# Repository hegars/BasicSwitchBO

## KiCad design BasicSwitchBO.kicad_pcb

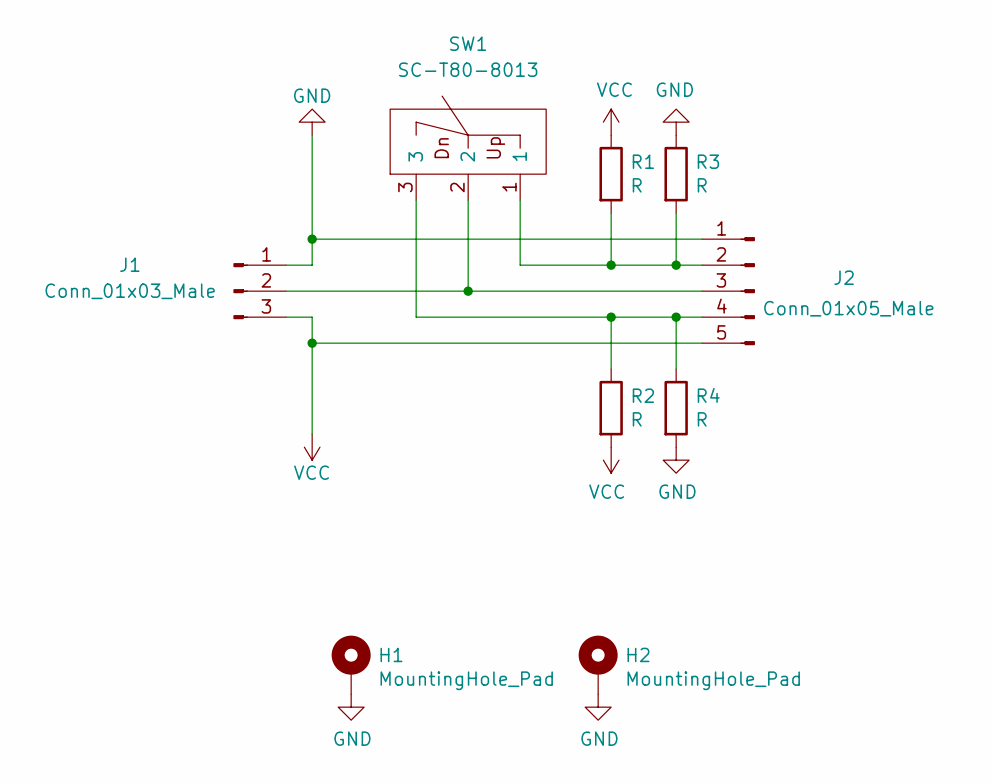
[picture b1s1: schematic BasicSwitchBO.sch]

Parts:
H1, H2: MountingHole_Pad; MountingHole_3.2mm_M3_Pad_Via
J1: Conn_01x03_Male; Pin_Header_Straight_1x03_Pitch2.54mm
J2: Conn_01x05_Male; Pin_Header_Straight_1x05_Pitch2.54mm
R1, R2, R3, R4: R; R_Axial_DIN0204_L3.6mm_D1.6mm_P1.90mm_Vertical
SW1: SC-T80-8013; Salecom T80-T T8013

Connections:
GND: H1.1, H2.1, J1.1, J2.1, R3.1, R4.2
unnamed: J1.2, J2.3, SW1.2
unnamed: J2.2, R1.2, R3.2, SW1.1
unnamed: J2.4, R2.1, R4.1, SW1.3
VCC: J1.3, J2.5, R1.1, R2.2

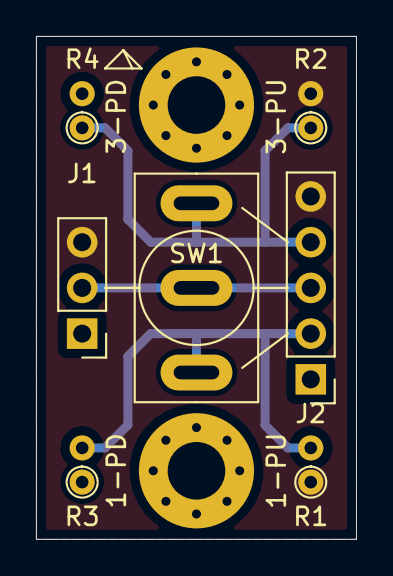
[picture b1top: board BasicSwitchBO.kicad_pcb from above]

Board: 2 copper layers, 17.8 x 27.9 mm, 9 parts (0 on the bottom side), 5 nets.

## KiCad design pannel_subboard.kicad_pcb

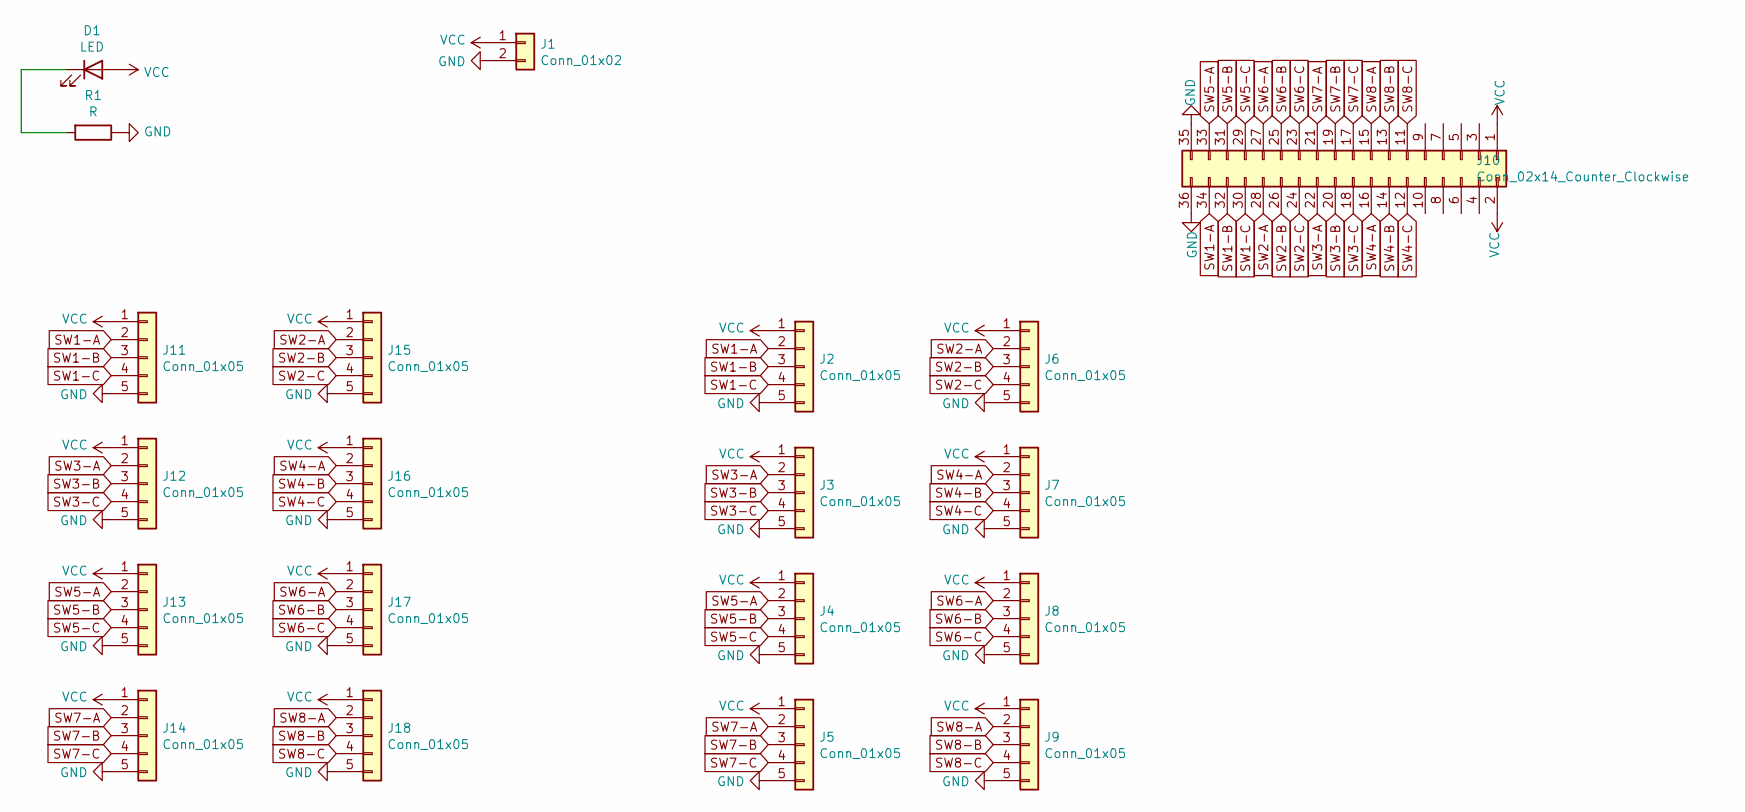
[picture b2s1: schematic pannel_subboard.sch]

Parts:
D1: LED; LED_D3.0mm
J1: Conn_01x02; Pin_Header_Straight_1x02_Pitch2.54mm
J2, J3, J4, J5, J6, J7, J8, J9, J11, J12, J13, J14, J15, J16, J17, J18: Conn_01x05; Pin_Header_Straight_1x05_Pitch2.54mm
J10: Conn_02x14_Counter_Clockwise; Pin_Header_Straight_2x18_Pitch2.54mm
R1: R; R_Axial_DIN0204_L3.6mm_D1.6mm_P1.90mm_Vertical

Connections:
GND: J1.2, J2.5, J3.5, J4.5, J5.5, J6.5, J7.5, J8.5, J9.5, J10.35, J10.36, J11.5, J12.5, J13.5, J14.5, J15.5, J16.5, J17.5, J18.5, R1.1
unnamed: D1.1 (K), R1.2
SW1-A: J2.2, J10.34, J11.2
SW1-B: J2.3, J10.32, J11.3
SW1-C: J2.4, J10.30, J11.4
SW2-A: J6.2, J10.28, J15.2
SW2-B: J6.3, J10.26, J15.3
SW2-C: J6.4, J10.24, J15.4
SW3-A: J3.2, J10.22, J12.2
SW3-B: J3.3, J10.20, J12.3
SW3-C: J3.4, J10.18, J12.4
SW4-A: J7.2, J10.16, J16.2
SW4-B: J7.3, J10.14, J16.3
SW4-C: J7.4, J10.12, J16.4
SW5-A: J4.2, J10.33, J13.2
SW5-B: J4.3, J10.31, J13.3
SW5-C: J4.4, J10.29, J13.4
SW6-A: J8.2, J10.27, J17.2
SW6-B: J8.3, J10.25, J17.3
SW6-C: J8.4, J10.23, J17.4
SW7-A: J5.2, J10.21, J14.2
SW7-B: J5.3, J10.19, J14.3
SW7-C: J5.4, J10.17, J14.4
SW8-A: J9.2, J10.15, J18.2
SW8-B: J9.3, J10.13, J18.3
SW8-C: J9.4, J10.11, J18.4
VCC: D1.2 (A), J1.1, J2.1, J3.1, J4.1, J5.1, J6.1, J7.1, J8.1, J9.1, J10.1, J10.2, J11.1, J12.1, J13.1, J14.1, J15.1, J16.1, J17.1, J18.1

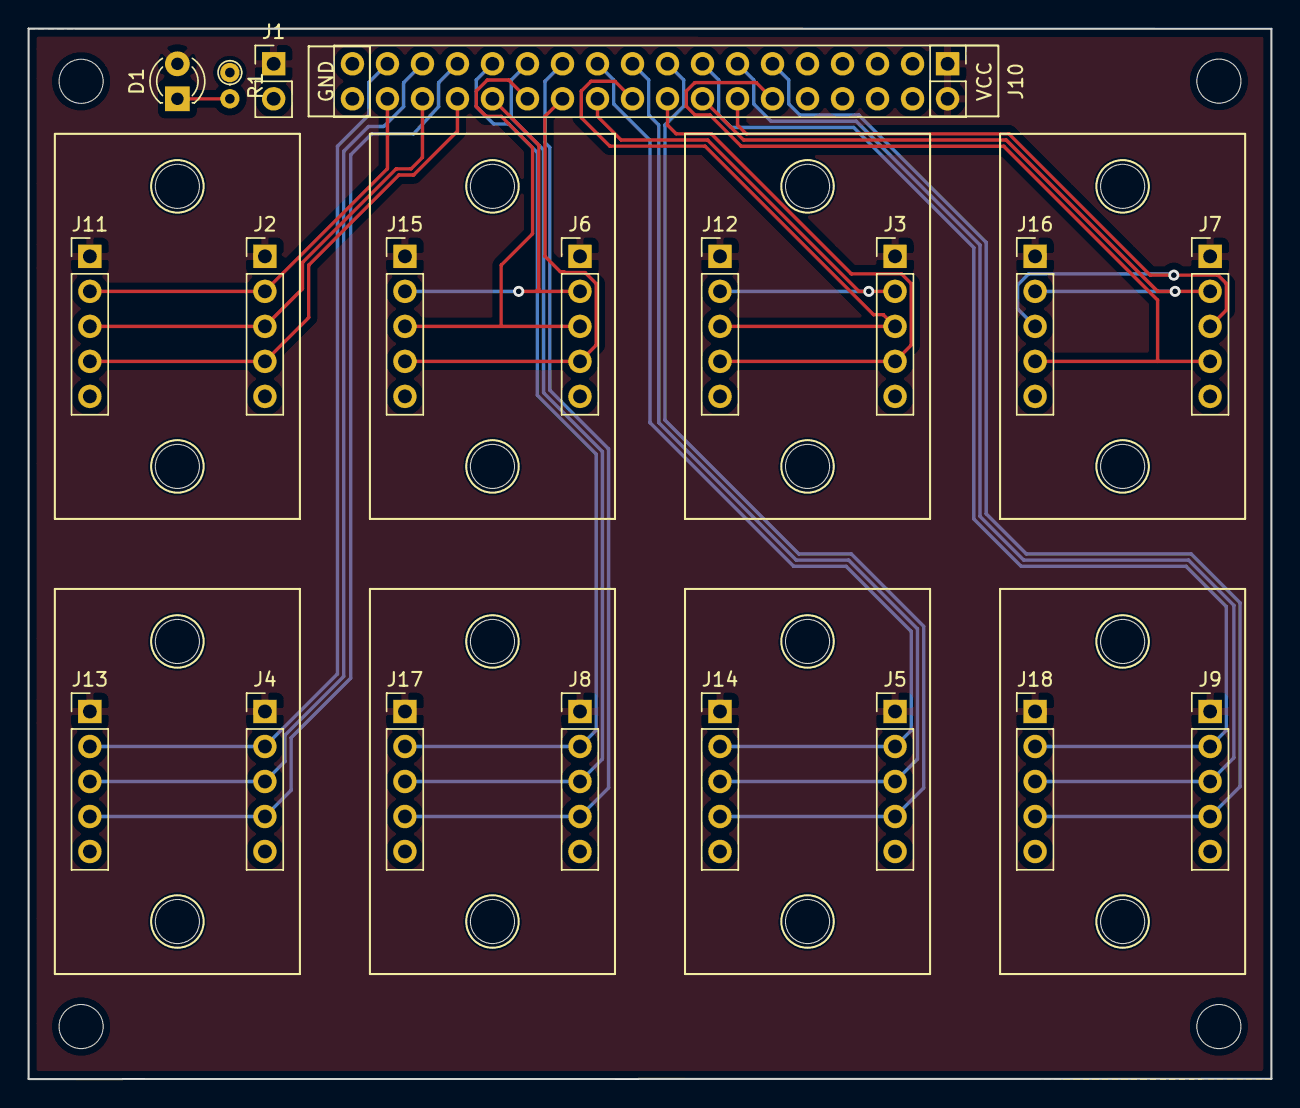
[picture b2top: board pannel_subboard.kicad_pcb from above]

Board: 2 copper layers, 90.2 x 76.2 mm, 20 parts (0 on the bottom side), 27 nets.

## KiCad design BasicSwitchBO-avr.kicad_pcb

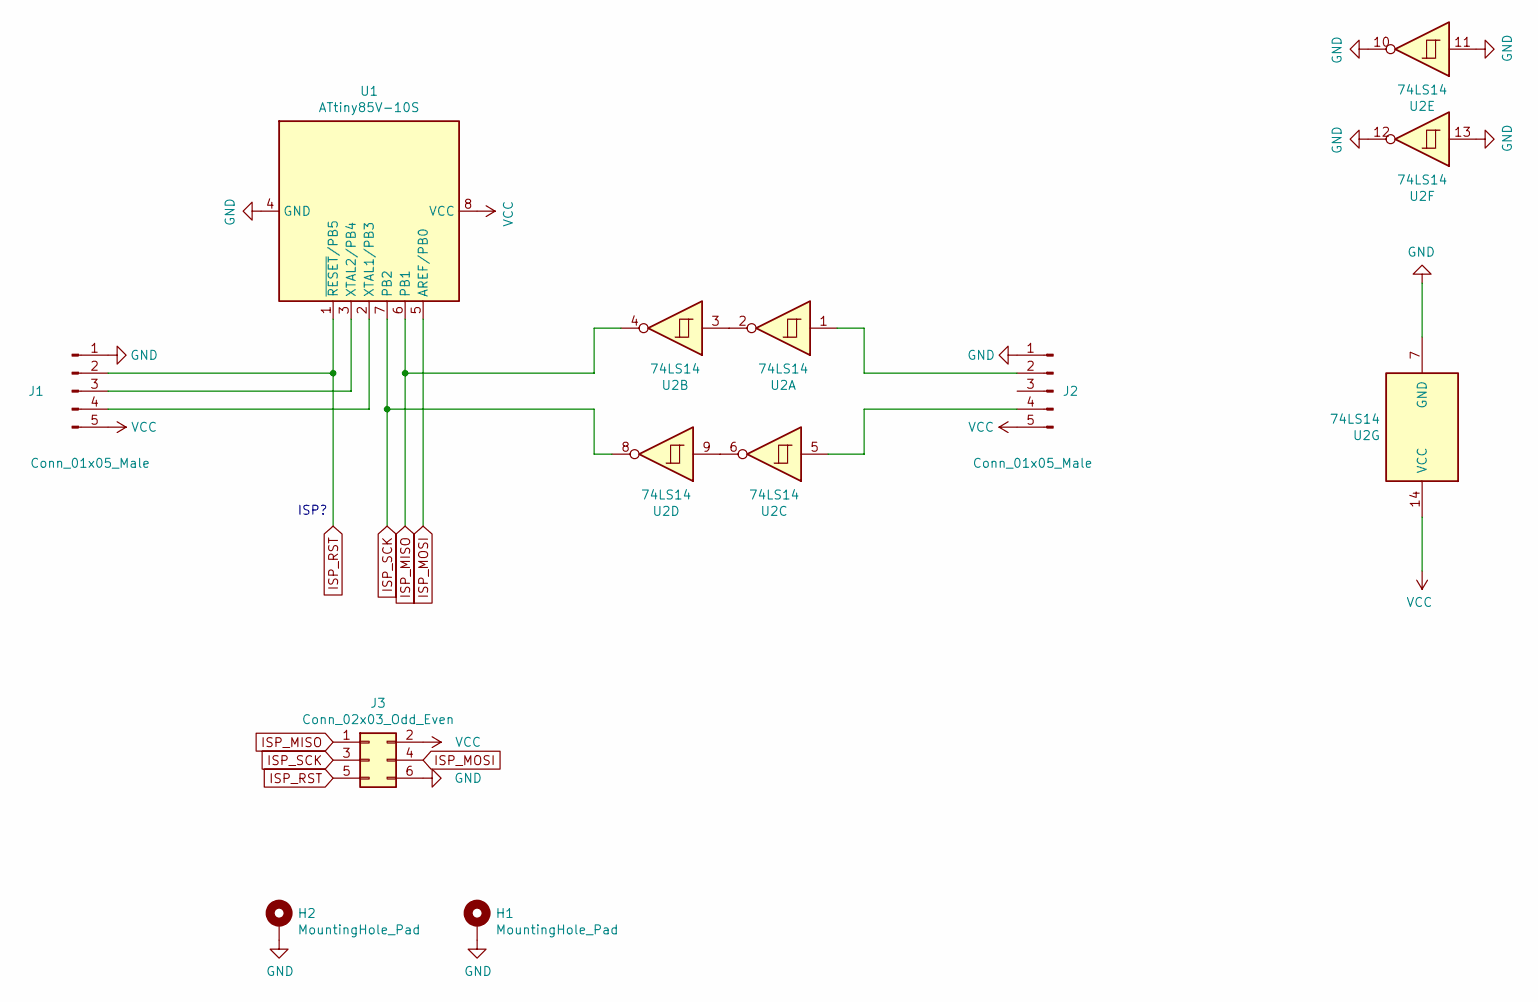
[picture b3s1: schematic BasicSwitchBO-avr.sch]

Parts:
H1, H2: MountingHole_Pad; MountingHole_3.2mm_M3_Pad_Via
J1, J2: Conn_01x05_Male; Pin_Header_Straight_1x05_Pitch2.54mm
J3: Conn_02x03_Odd_Even; Pin_Header_Straight_2x03_Pitch1.27mm
U1: ATtiny85V-10S; SOIC-8_3.9x4.9mm_Pitch1.27mm
U2: 74LS14; SOIC-14_3.9x8.7mm_Pitch1.27mm

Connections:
GND: H1.1, H2.1, J1.1, J2.1, J3.6, U1.4 (GND), U2.7 (GND), U2.10, U2.11, U2.12, U2.13
ISP_MISO: J3.1, U1.6 (PB1), U2.4
ISP_MOSI: J3.4, U1.5 (AREF/PB0)
ISP_RST: J1.2, J3.5, U1.1 (~RESET~/PB5)
ISP_SCK: J3.3, U1.7 (PB2), U2.8
unnamed: J1.3, U1.3 (XTAL2/PB4)
unnamed: J1.4, U1.2 (XTAL1/PB3)
unnamed: J2.2, U2.1
unnamed: J2.4, U2.5
unnamed: U2.2, U2.3
unnamed: U2.6, U2.9
VCC: J1.5, J2.5, J3.2, U1.8 (VCC), U2.14 (VCC)

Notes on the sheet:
ISP?

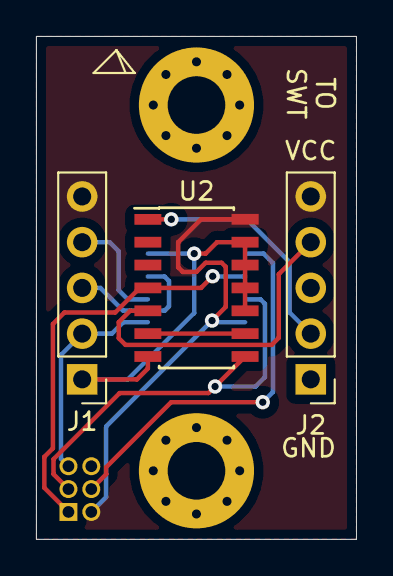
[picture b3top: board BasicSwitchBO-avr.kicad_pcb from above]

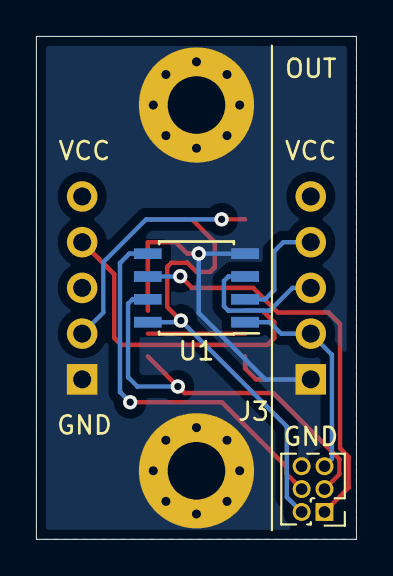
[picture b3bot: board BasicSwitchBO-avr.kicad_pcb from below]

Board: 2 copper layers, 17.8 x 27.9 mm, 7 parts (2 on the bottom side), 12 nets.

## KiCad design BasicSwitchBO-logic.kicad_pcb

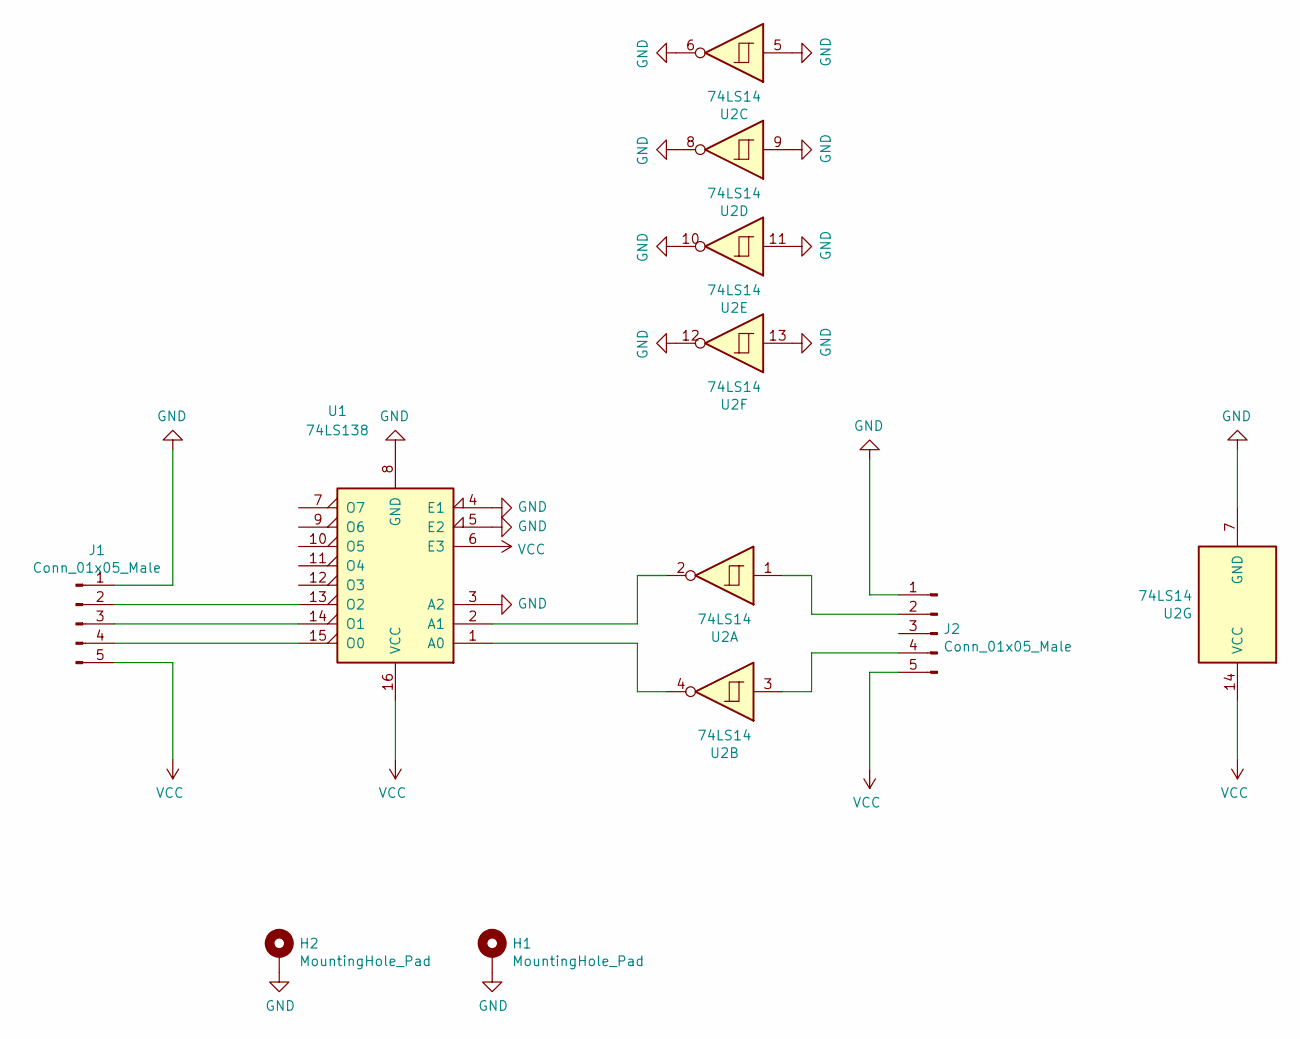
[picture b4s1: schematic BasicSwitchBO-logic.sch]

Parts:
H1, H2: MountingHole_Pad; MountingHole_3.2mm_M3_Pad_Via
J1, J2: Conn_01x05_Male; Pin_Header_Straight_1x05_Pitch2.54mm
U1: 74LS138; SOIC-16_3.9x9.9mm_Pitch1.27mm
U2: 74LS14; SOIC-14_3.9x8.7mm_Pitch1.27mm

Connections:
GND: H1.1, H2.1, J1.1, J2.1, U1.3 (A2), U1.4 (E1), U1.5 (E2), U1.8 (GND), U2.5, U2.6, U2.7 (GND), U2.8, U2.9, U2.10, U2.11, U2.12, U2.13
unnamed: J1.2, U1.13 (O2)
unnamed: J1.3, U1.14 (O1)
unnamed: J1.4, U1.15 (O0)
unnamed: J2.2, U2.1
unnamed: J2.4, U2.3
unnamed: U1.1 (A0), U2.4
unnamed: U1.2 (A1), U2.2
VCC: J1.5, J2.5, U1.6 (E3), U1.16 (VCC), U2.14 (VCC)

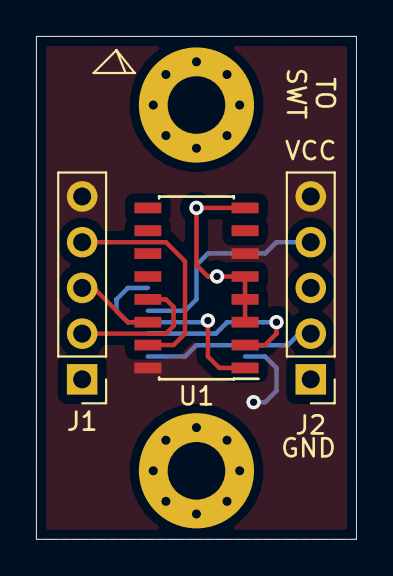
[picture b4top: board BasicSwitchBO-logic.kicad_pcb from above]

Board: 2 copper layers, 17.8 x 27.9 mm, 6 parts (1 on the bottom side), 9 nets.

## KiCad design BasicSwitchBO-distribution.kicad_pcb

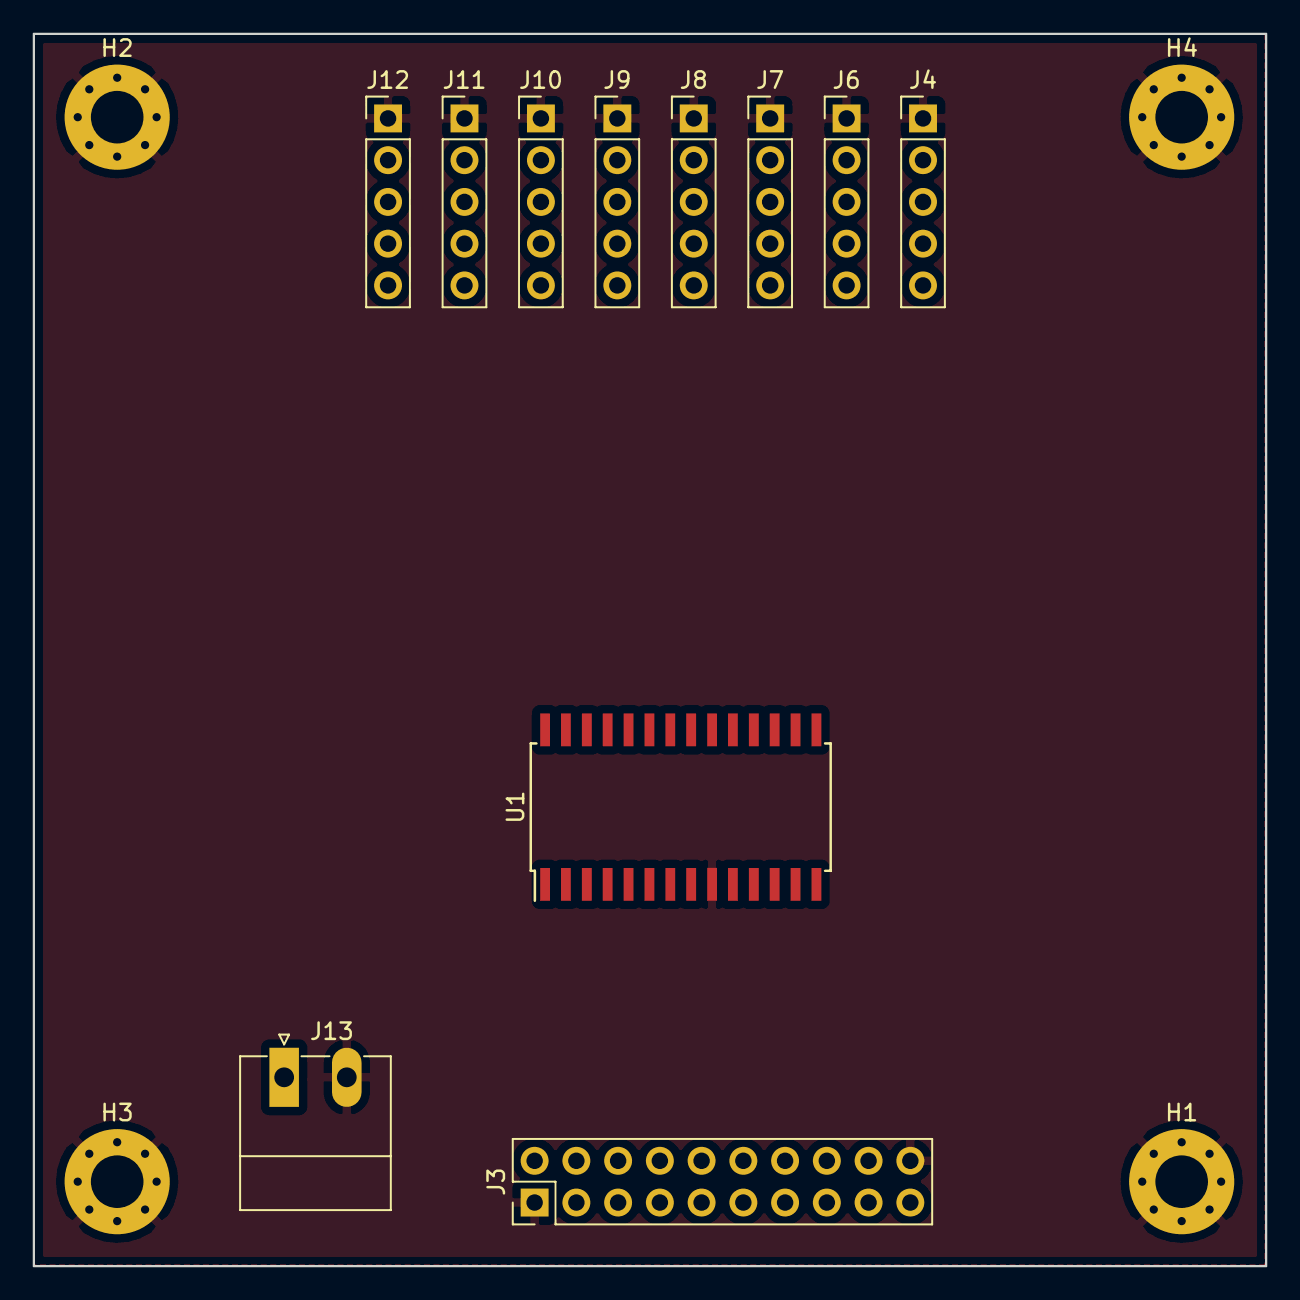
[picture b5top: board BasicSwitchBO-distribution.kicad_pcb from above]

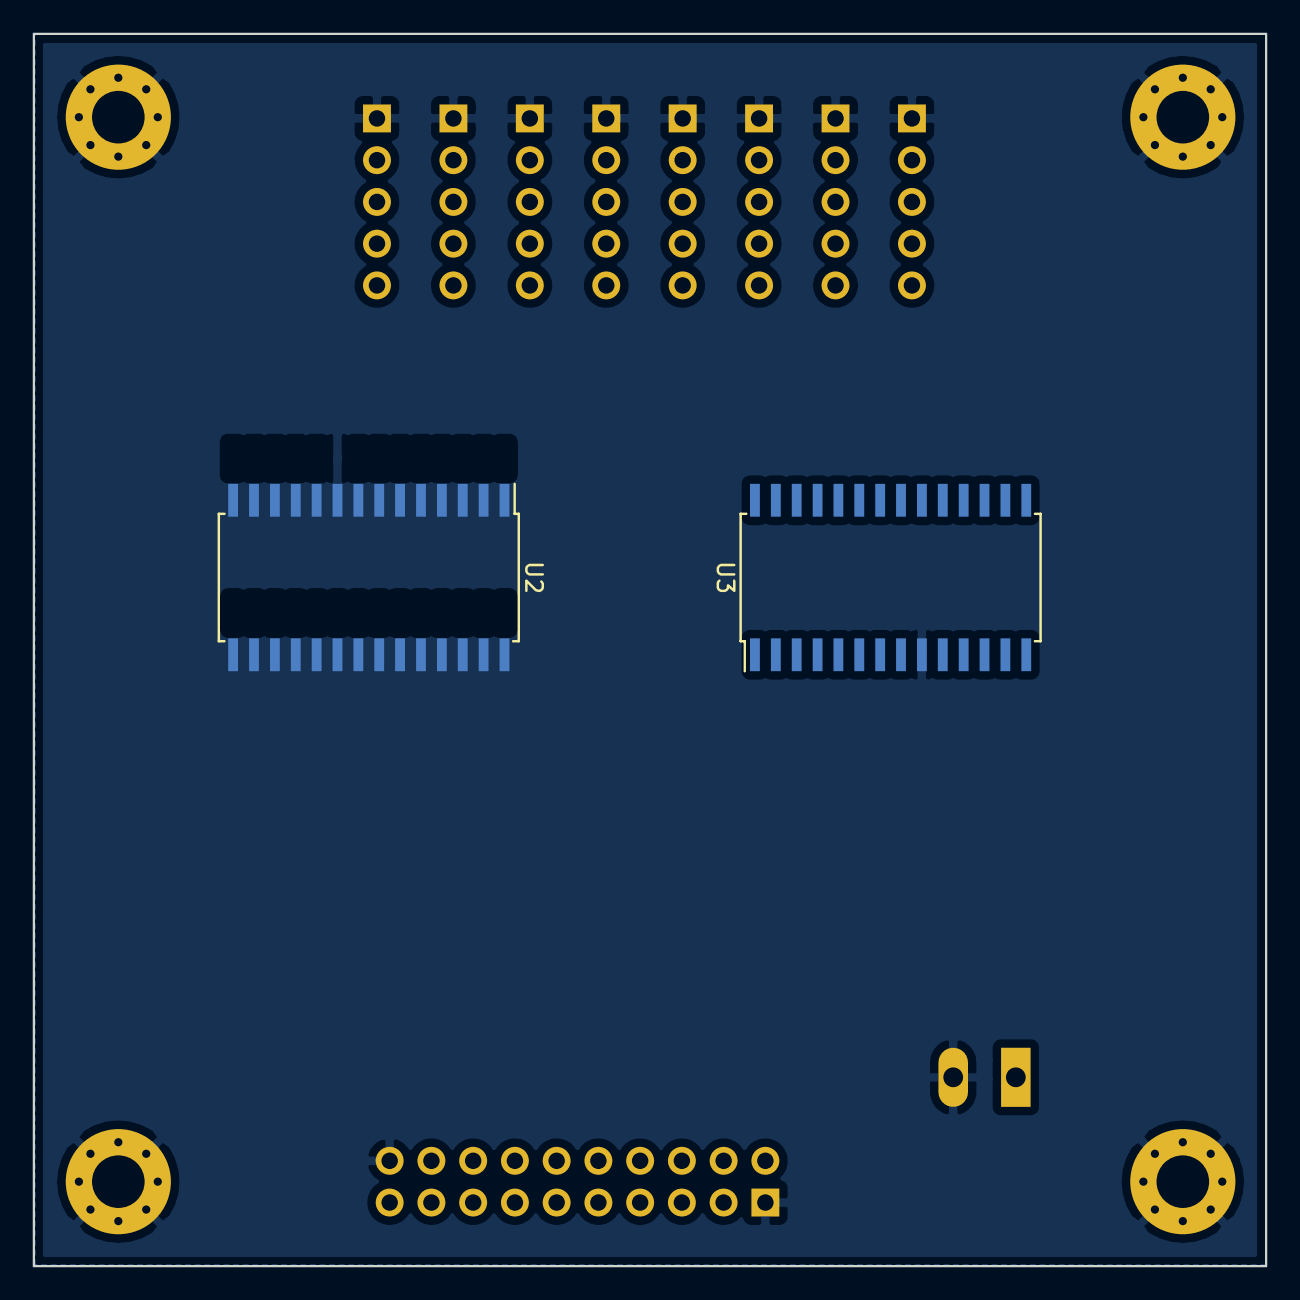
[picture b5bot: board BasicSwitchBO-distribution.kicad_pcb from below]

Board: 2 copper layers, 75.0 x 75.0 mm, 17 parts (2 on the bottom side), 27 nets, no tracks yet.

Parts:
H1, H2, H3, H4: MountingHole_Pad; MountingHole_3.2mm_M3_Pad_Via
J3: Conn_01x10_Male; Pin_Header_Straight_2x10_Pitch2.54mm
J4, J6, J7, J8, J9, J10, J11, J12: Conn_01x05_Male; Pin_Header_Straight_1x05_Pitch2.54mm
J13: Conn_01x02; PhoenixContact_MC-G_02x3.81mm_Angled
U1, U2, U3: MCP23017_SP; SOIC-28W_7.5x17.9mm_Pitch1.27mm

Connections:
+5V: J4.5, J6.5, J7.5, J8.5, J9.5, J10.5, J11.5, J12.5, U1.10, U2.10, U3.10
+24V: J3.10, J3.11, J13.1
GND: H1.1, H2.1, H3.1, H4.1, J3.1, J3.20, J4.1, J6.1, J7.1, J8.1, J9.1, J10.1, J11.1, J12.1, J13.2, U1.9, U2.9, U3.9
SW1_0: J4.4, U2.21
SW1_1: J4.3, U2.22
SW1_2: J4.2, U2.23
SW2_0: J6.4, U2.24
SW2_1: J6.3, U2.25
SW2_2: J6.2, U2.26
SW3_0: J7.4, U2.27
SW3_1: J7.3, U2.28
SW3_2: J7.2, U2.1
SW4_0: J8.4, U2.2
SW4_1: J8.3, U2.3
SW4_2: J8.2, U2.4
SW5_0: J9.4, U2.5
SW5_1: J9.3, U2.6
SW5_2: J9.2, U2.7
SW6_0: J10.4, U2.8
SW6_1: J10.3, U3.21
SW6_2: J10.2, U3.22
SW7_0: J11.4, U3.23
SW7_1: J11.3, U3.24
SW7_2: J11.2, U3.25
SW8_0: J12.4, U3.26
SW8_1: J12.3, U3.27
SW8_2: J12.2, U3.28

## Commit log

2021-10-19 init
